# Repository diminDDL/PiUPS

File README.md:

# The DDL pi UPS

# Terms of use
### The following conditions should be met if you want to use any part of this repository:

By using this project or its parts, for any purpose and in any shape or form, you grant your **implicit agreement** to all the following statements:

- You **condemn Russia and its military aggression against Ukraine**
- You **recognize that Russia is an occupant that unlawfully invaded a sovereign state**
- You **support Ukraine's territorial integrity, including its claims over temporarily occupied territories of Crimea and Donbas**
- You **reject false narratives perpetuated by Russian state propaganda**

To learn more about the war and how you can help, [click here](https://u24.gov.ua/). Glory to Ukraine! 🇺🇦

### AND

## CERN Open Hardware Licence v2 (CERN-OHL-W) TL;DR

- **Can:**
  - *Use*: You are free to use the hardware design in any way.
  - *Modify*: You can make modifications to the design.
  - *Distribute*: You can share the original or modified design with others.
  - *Commercial Use*: You can use the design in commercial projects.

- **Can't:**
  - *Hold Liable*: The original author is not liable for any damages or consequences resulting from the use of the design.

- **Conditions:**
  - *Attribution*: You must give appropriate credit to the original author, including a copyright notice, a link to the license, and an indication of any changes made.
  - *ShareAlike*: If you modify the design, you must distribute your contributions under the same license as the original.
  - *License Notice*: You must include a copy of the CERN-OHL-W v2 with the distributed design or provide a clear link to the license.

Disclaimer: This summary is not a legal document and does not provide legal advice. Please read the full license text for a complete understanding of its terms and conditions.

## Info

This repo contains the hardware and *soon TM* software for the ultra efficient raspberry pi UPS.
The reason this was created was because I wasn't satisfied with the things available on the market
that would just lower the incoming voltage to charge the battery and immediately boost it to power the pi. This way efficiencies of around ~80% can be achieved. Don't get me wrong this is not terrible but I wanted to do better, which is why this design incorporates a power MUX.

### Current revision: 0.5

##### Known issues of rev 0.5

| Issue  | Possible fix |
| ------------- |:-------------:|
| Power mux and everything involving the comparator oscilates when trying to shut down. | Use TL431 instead, it combines a voltage reference and a comparator. |
| Turning switch off while plugged in doesn't turn off the output. | Rework the schematic. |
| DW01 chip is acting up (high leakage, not working half of the time). | Replace with BQ2970. |
| BMS turns off when the charger is plugged in. | Try removing diodes going to the fs8205. |

### Pictures

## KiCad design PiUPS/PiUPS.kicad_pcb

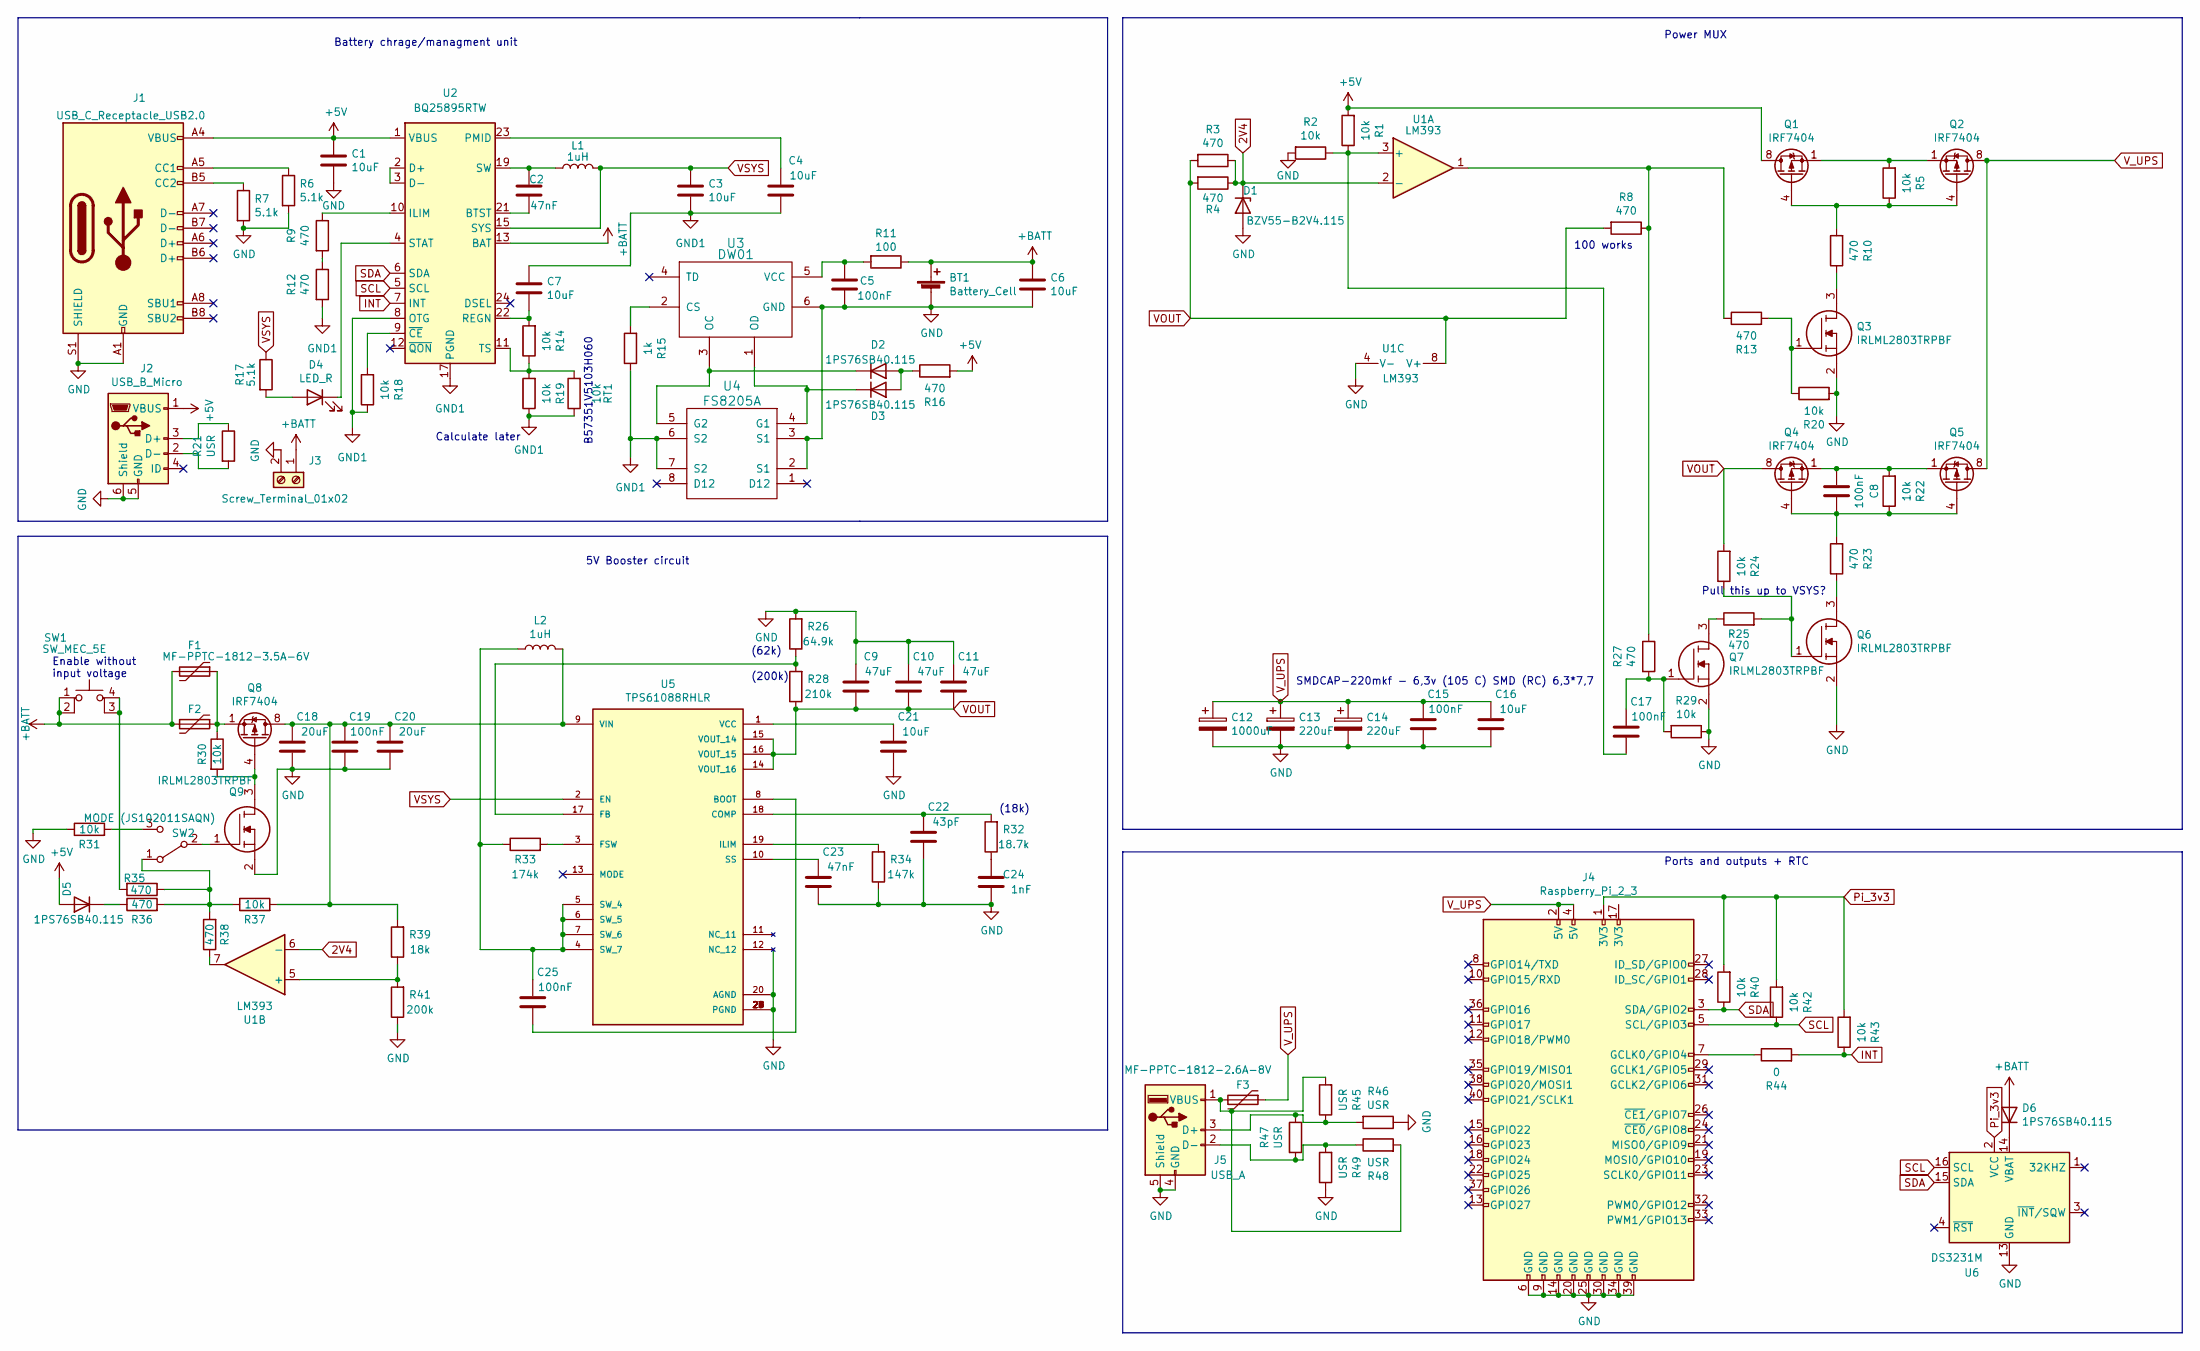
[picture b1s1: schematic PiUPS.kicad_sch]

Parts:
BT1: Battery_Cell; BatteryHolder_Keystone_1042_1x18650
C1, C3, C4, C6, C7, C16, C21: 10uF; C_1206_3216Metric_Pad1.33x1.80mm_HandSolder
C2, C23: 47nF; C_0805_2012Metric_Pad1.18x1.45mm_HandSolder
C5, C8, C15, C17, C19, C25: 100nF; C_0805_2012Metric_Pad1.18x1.45mm_HandSolder
C9, C10, C11: 47uF; C_1210_3225Metric_Pad1.33x2.70mm_HandSolder
C12: 1000uF; CP_Elec_10x10
C13, C14: 220uF; CP_Elec_6.3x7.7
C18, C20: 20uF; C_1206_3216Metric_Pad1.33x1.80mm_HandSolder
C22: 43pF; C_0805_2012Metric_Pad1.18x1.45mm_HandSolder
C24: 1nF; C_0805_2012Metric_Pad1.18x1.45mm_HandSolder
D1: BZV55-B2V4.115; D_1206_3216Metric_Pad1.42x1.75mm_HandSolder
D2, D3, D5, D6: 1PS76SB40.115; D_SOD-323_HandSoldering
D4: LED_R; LED_1206_3216Metric_Pad1.42x1.75mm_HandSolder
F1, F2: MF-PPTC-1812-3.5A-6V; Fuse_1812_4532Metric_Pad1.30x3.40mm_HandSolder
F3: MF-PPTC-1812-2.6A-8V; Fuse_1812_4532Metric_Pad1.30x3.40mm_HandSolder
J1: USB_C_Receptacle_USB2.0; USB_C_Receptacle_Palconn_UTC16-G
J2: USB_B_Micro; USB_Micro-B_Amphenol_10103594-0001LF_Horizontal
J3: Screw_Terminal_01x02; TerminalBlock_Altech_AK300-2_P5.00mm
J4: Raspberry_Pi_2_3; raspberrypi_2_3
J5: USB_A; SAMTEC_USB-A-S-X-X-SM2
L1: 1uH; L_6.3x6.3_H3
L2: 1uH; L_10.4x10.4_H4.8
Q1, Q2, Q4, Q5, Q8: IRF7404; SOIC-8_3.9x4.9mm_P1.27mm
Q3, Q6, Q7, Q9: IRLML2803TRPBF; SOT95P237X112-3N; Manufacturer_Part_Number IRLML2803TRPBF; Mouser Part Number 942-IRLML2803TRPBF
R1, R2, R5, R14, R18, R19, R20, R22, R24, R29, R30, R31, R37, R40, R42, R43: 10k; R_0805_2012Metric_Pad1.20x1.40mm_HandSolder
R3, R4, R8, R9, R10, R12, R13, R16, R23, R25, R27, R35, R36, R38: 470; R_0805_2012Metric_Pad1.20x1.40mm_HandSolder
R6, R7, R17: 5.1k; R_0805_2012Metric_Pad1.20x1.40mm_HandSolder
R11: 100; R_0805_2012Metric_Pad1.20x1.40mm_HandSolder
R15: 1k; R_0805_2012Metric_Pad1.20x1.40mm_HandSolder
R21, R45, R46, R47, R48, R49: USR; R_0805_2012Metric_Pad1.20x1.40mm_HandSolder
R26: 64.9k; R_0805_2012Metric_Pad1.20x1.40mm_HandSolder
R28: 210k; R_0805_2012Metric_Pad1.20x1.40mm_HandSolder
R32: 18.7k; R_0805_2012Metric_Pad1.20x1.40mm_HandSolder
R33: 174k; R_0805_2012Metric_Pad1.20x1.40mm_HandSolder
R34: 147k; R_0805_2012Metric_Pad1.20x1.40mm_HandSolder
R39: 18k; R_0805_2012Metric_Pad1.20x1.40mm_HandSolder
R41: 200k; R_0805_2012Metric_Pad1.20x1.40mm_HandSolder
R44: 0; R_0805_2012Metric_Pad1.20x1.40mm_HandSolder
RT1: 10k; R_0603_1608Metric
SW1: SW_MEC_5E; SW_SPST_Omron_B3FS-100xP
SW2: MODE (JS102011SAQN); SW_SPDT_CK-JS102011SAQN
U1: LM393; SOIC-8_3.9x4.9mm_P1.27mm
U2: BQ25895RTW; Texas_S-PWQFN-N24_EP2.7x2.7mm_ThermalVias
U3: DW01; SOT-23-6
U4: FS8205A; TSSOP-8_4.4x3mm_P0.65mm
U5: TPS61088RHLR; IC_TPS61088RHLR; PARTREV 4219071/A 05/2017
U6: DS3231M; SOIC-16W_7.5x10.3mm_P1.27mm

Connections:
2V4: D1.1 (K), R3.1, R4.1, U1.2 (-), U1.6 (-)
+5V: C1.1, D5.2 (A), J1.A4 (VBUS), J1.A9 (VBUS), J1.B4 (VBUS), J1.B9 (VBUS), J2.1 (VBUS), Q1.5 (D), Q1.6 (D), Q1.7 (D), Q1.8 (D), R1.2, R16.2, U2.1 (VBUS)
+BATT: BT1.1 (+), C6.1, D6.2 (A), F1.2, F2.2, J3.1, R11.1, SW1.1, SW1.2, U2.13 (BAT), U2.14 (BAT)
GND: BT1.2 (-), C1.2, C5.2, C6.2, C9.1, C10.1, C11.1, C12.2, C13.2, C14.2, C15.2, C16.2, C18.2, C19.2, C20.2, C21.2, C22.2, C23.2, C24.2, D1.2 (A), J1.A1 (GND), J1.A12 (GND), J1.B1 (GND), J1.B12 (GND), J1.S1 (SHIELD), J2.5 (GND), J2.6 (Shield), J3.2, J4.6 (GND), J4.9 (GND), J4.14 (GND), J4.20 (GND), J4.25 (GND), J4.30 (GND), J4.34 (GND), J4.39 (GND), J5.4 (GND), J5.5 (Shield), Q3.2, Q6.2, Q7.2, Q9.2, R2.2, R6.2, R7.2, R20.2, R26.2, R29.1, R31.1, R34.1, R41.1, R46.1, R49.1, U1.4 (V-), U3.6 (GND), U4.2 (S1), U4.3 (S1), U5.12 (NC_12), U5.20 (AGND), U5.21 (PGND), U5.22 (PGND), U5.23 (PGND), U5.24 (PGND), U5.25 (PGND), U5.26 (PGND), U5.27 (PGND), U5.28 (PGND), U5.29 (PGND), U6.5 (GND), U6.6 (GND), U6.7 (GND), U6.8 (GND), U6.9 (GND), U6.10 (GND), U6.11 (GND), U6.12 (GND), U6.13 (GND); also elsewhere on the board
GND1: C3.2, C4.2, C7.1, R12.2, R15.1, R18.1, R19.1, RT1.1, U2.8 (OTG), U2.17 (PGND), U2.18 (PGND), U2.25 (PGND), U4.6 (S2), U4.7 (S2)
INT: R43.1, R44.2, U2.7 (INT)
unnamed: C2.1, L1.1, U2.19 (SW), U2.20 (SW)
unnamed: C2.2, U2.21 (BTST)
unnamed: C4.1, U2.23 (PMID)
unnamed: C5.1, R11.2, U3.5 (VCC)
unnamed: C7.2, R14.2, U2.22 (REGN)
unnamed: C8.1, Q4.1 (S), Q4.2 (S), Q4.3 (S), Q5.1 (S), Q5.2 (S), Q5.3 (S), R22.2
unnamed: C8.2, Q4.4 (G), Q5.4 (G), R22.1, R23.2
unnamed: C17.1, Q7.1, R27.2, R29.2
unnamed: C17.2, R1.1, R2.1, U1.3 (+)
unnamed: C18.1, C19.1, C20.1, L2.2, Q8.5 (D), Q8.6 (D), Q8.7 (D), Q8.8 (D), R37.2, R39.2, U5.9 (VIN)
unnamed: C21.1, U5.1 (VCC)
unnamed: C22.1, R32.2, U5.18 (COMP)
unnamed: C23.1, U5.10 (SS)
unnamed: C24.1, R32.1
unnamed: C25.1, L2.1, R33.1, U5.4 (SW_7), U5.5 (SW_4), U5.6 (SW_5), U5.7 (SW_6)
unnamed: C25.2, U5.8 (BOOT)
unnamed: D2.1 (K), U3.3 (OC), U4.5 (G2)
unnamed: D2.2 (A), D3.2 (A), R16.1
unnamed: D3.1 (K), U3.1 (OD), U4.4 (G1)
unnamed: D4.1 (K), U2.4 (STAT)
unnamed: D4.2 (A), R17.2
unnamed: D5.1 (K), R36.1
unnamed: D6.1 (K), U6.14 (VBAT)
unnamed: F1.1, F2.1, Q8.1 (S), Q8.2 (S), Q8.3 (S), R30.1
unnamed 30: F3.2, J5.1 (VBUS), R45.2, R48.2; also elsewhere on the board
unnamed: J1.A5 (CC1), R6.1
unnamed: J1.B5 (CC2), R7.1
unnamed: J2.2 (D-), R21.2
unnamed: J2.3 (D+), R21.1
unnamed: J4.7 (GCLK0/GPIO4), R44.1
unnamed: J5.2 (D-), R47.2, R48.1, R49.2
unnamed: J5.3 (D+), R45.1, R46.2, R47.1
unnamed: Q1.1 (S), Q1.2 (S), Q1.3 (S), Q2.1 (S), Q2.2 (S), Q2.3 (S), R5.2
unnamed: Q1.4 (G), Q2.4 (G), R5.1, R10.2
unnamed: Q3.1, R13.2, R20.1
unnamed: Q3.3, R10.1
unnamed: Q6.1, R24.1, R25.2
unnamed: Q6.3, R23.1
unnamed: Q7.3, R25.1
unnamed: Q8.4 (G), Q9.3, R30.2
unnamed: Q9.1, SW2.2 (B)
unnamed: R9.1, U2.10 (ILIM)
unnamed: R9.2, R12.1
unnamed: R8.1, R13.1, R27.1, U1.1
unnamed: R14.1, R19.2, RT1.2, U2.11 (TS)
unnamed: R15.2, U3.2 (CS)
unnamed: R18.2, U2.9 (~CE)
unnamed: R26.1, R28.2, U5.17 (FB)
unnamed: R31.2, SW2.3 (C)
unnamed: R33.2, U5.3 (FSW)
unnamed: R34.2, U5.19 (ILIM)
unnamed: R35.1, R36.2, R37.1, R38.2, SW2.1 (A)
unnamed: R35.2, SW1.3 (K), SW1.4 (A)
unnamed: R38.1, U1.7
unnamed: R39.1, R41.2, U1.5 (+)
unnamed: U2.2 (D+), U2.3 (D-)
Pi_3v3: J4.1 (3V3), R40.2, R42.2, R43.2, U6.2 (VCC)
SCL: J4.5 (SCL/GPIO3), R42.1, U2.5 (SCL), U6.16 (SCL)
SDA: J4.3 (SDA/GPIO2), R40.1, U2.6 (SDA), U6.15 (SDA)
VOUT: C9.2, C10.2, C11.2, Q4.5 (D), Q4.6 (D), Q4.7 (D), Q4.8 (D), R3.2, R4.2, R8.2, R24.2, R28.1, U1.8 (V+), U5.14 (VOUT_16), U5.15 (VOUT_14), U5.16 (VOUT_15)
VSYS: C3.1, L1.2, R17.1, U2.15 (SYS), U2.16 (SYS), U5.2 (EN)
V_UPS: C12.1, C13.1, C14.1, C15.1, C16.1, F3.1, J4.2 (5V), J4.4 (5V), Q2.5 (D), Q2.6 (D), Q2.7 (D), Q2.8 (D), Q5.5 (D), Q5.6 (D), Q5.7 (D), Q5.8 (D)

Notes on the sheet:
Enable without input voltage
Battery chrage/managment unit
Ports and outputs + RTC
5V Booster circuit
Calculate later
(200k)
(18k)
Power MUX
Pull this up to VSYS?
(62k)
B57351V5103H060
SMDCAP-220mkf - 6,3v (105 С) SMD (RC) 6,3*7,7
100 works

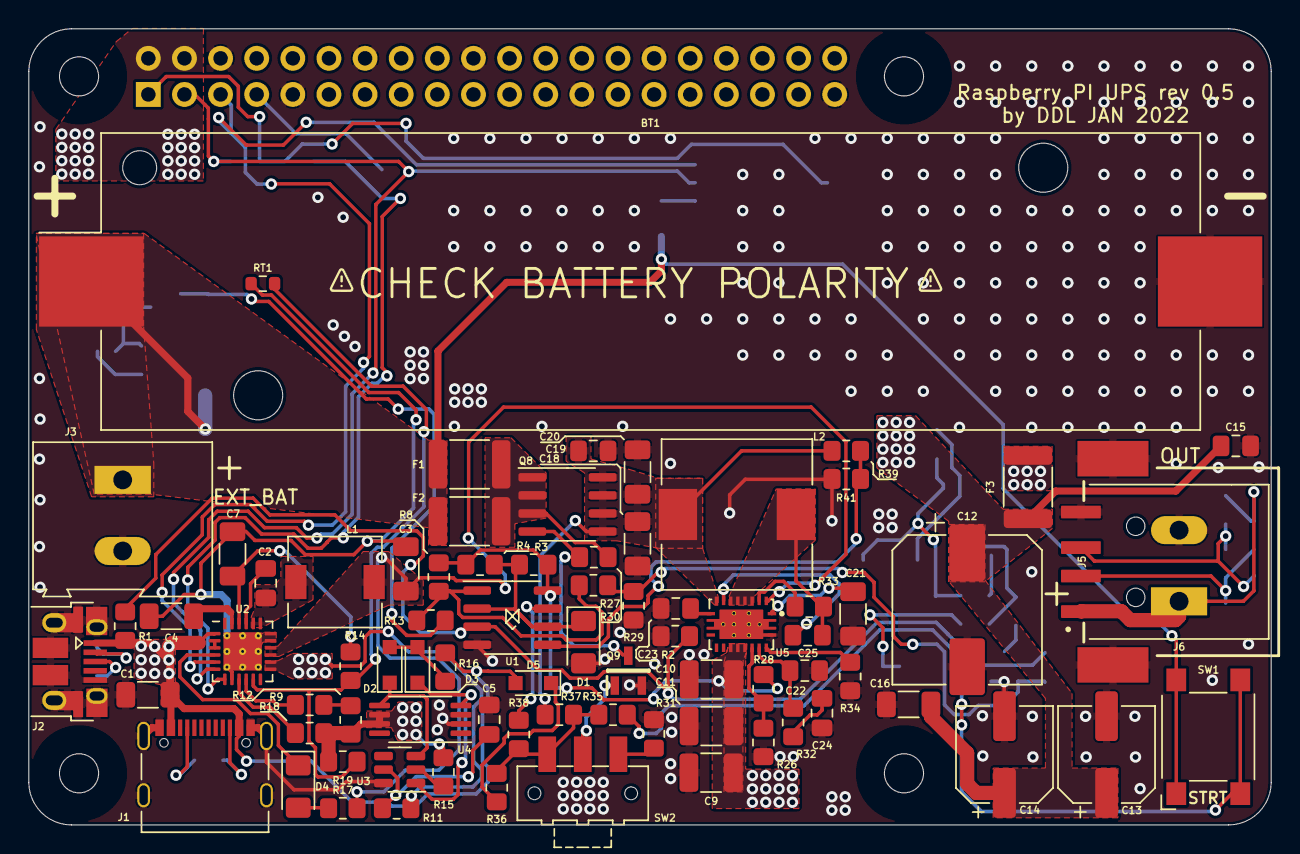
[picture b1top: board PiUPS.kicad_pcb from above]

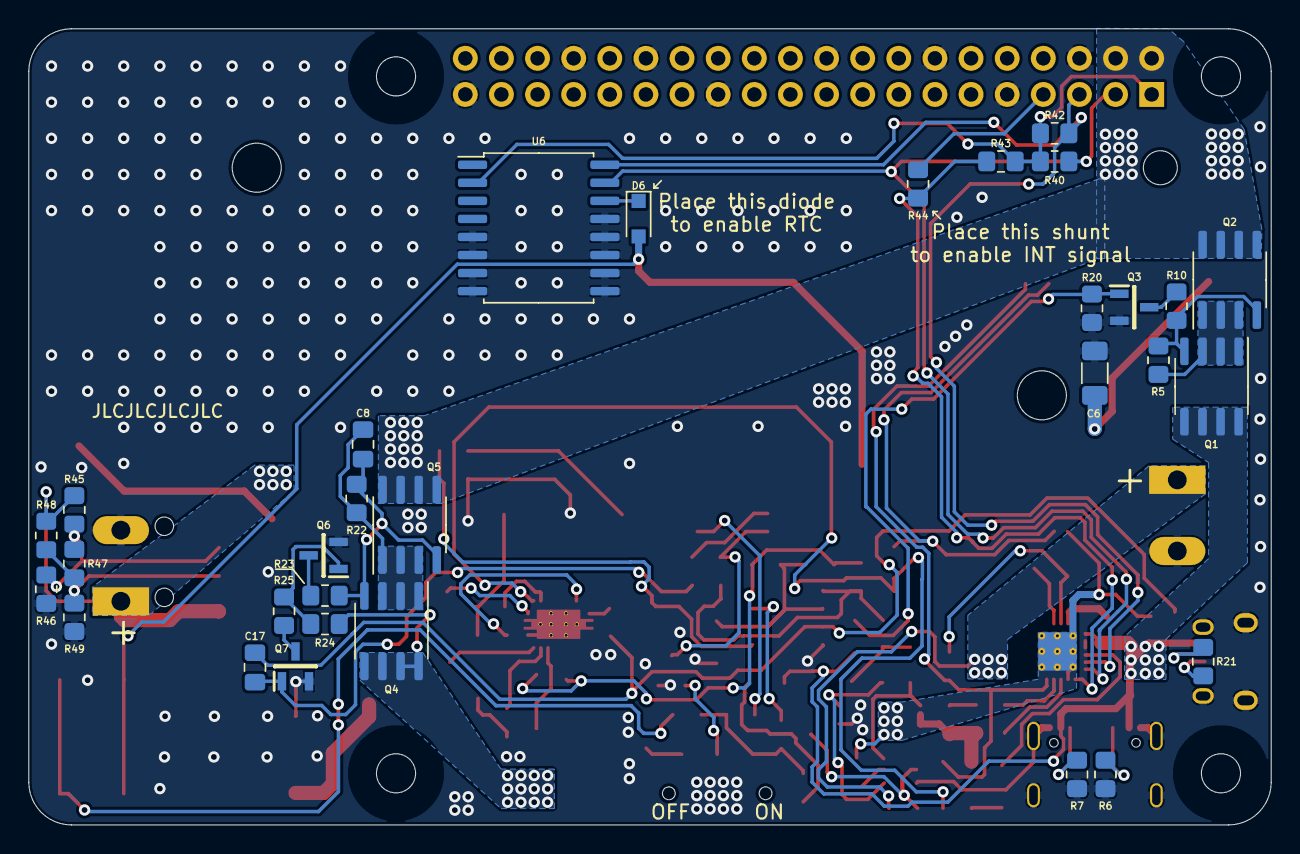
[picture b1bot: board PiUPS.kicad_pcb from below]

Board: 2 copper layers, 87.4 x 56.0 mm, 110 parts (31 on the bottom side), 68 nets.

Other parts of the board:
J6: Screw_Terminal_01x02; TerminalBlock_Altech_AK300-2_P5.00mm

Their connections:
GND: J6.2; also elsewhere on the board
unnamed 30: J6.1; also elsewhere on the board

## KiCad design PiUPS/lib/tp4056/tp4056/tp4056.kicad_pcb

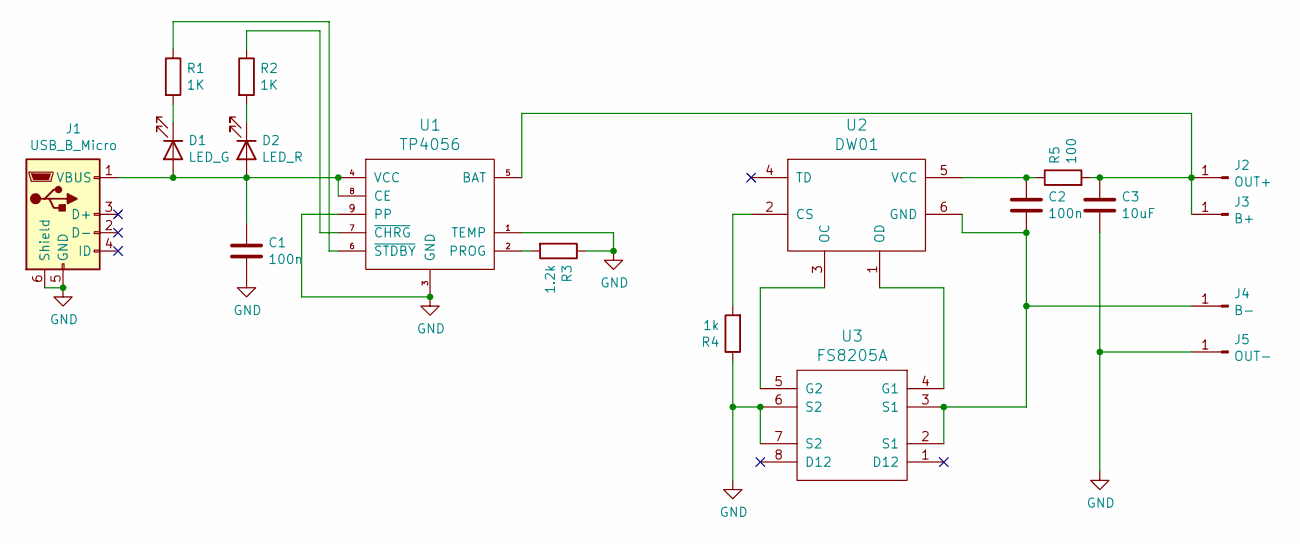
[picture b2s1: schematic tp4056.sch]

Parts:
C1, C2: 100n; C_0402_1005Metric_Pad0.74x0.62mm_HandSolder
C3: 10uF; C_0805_2012Metric_Pad1.18x1.45mm_HandSolder
D1: LED_G; C_0805_2012Metric_Pad1.18x1.45mm_HandSolder
D2: LED_R; C_0805_2012Metric_Pad1.18x1.45mm_HandSolder
J1: USB_B_Micro; USB_Micro-AB_Molex_47590-0001
J2: OUT+; PinHeader_1x01_P2.54mm_Vertical
J3: B+; PinHeader_1x01_P2.54mm_Vertical
J4: B-; PinHeader_1x01_P2.54mm_Vertical
J5: OUT-; PinHeader_1x01_P2.54mm_Vertical
R1, R2: 1K; R_0805_2012Metric_Pad1.20x1.40mm_HandSolder
R3: 1.2k; R_0805_2012Metric_Pad1.20x1.40mm_HandSolder
R4: 1k; R_0805_2012Metric_Pad1.20x1.40mm_HandSolder
R5: 100; R_0805_2012Metric_Pad1.20x1.40mm_HandSolder
U1: TP4056; SOIC-8-1EP_3.9x4.9mm_P1.27mm_EP2.29x3mm
U2: DW01; TSOP-6_1.65x3.05mm_P0.95mm
U3: FS8205A; TSSOP-8_4.4x3mm_P0.65mm

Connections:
GND: C1.2, C3.2, J1.5 (GND), J1.6 (Shield), J5.1, R3.1, R4.1, U1.1 (TEMP), U1.3 (GND), U1.9 (PP), U3.6 (S2), U3.7 (S2)
unnamed: C1.1, D1.2 (A), D2.2 (A), J1.1 (VBUS), U1.4 (VCC), U1.8 (CE)
unnamed: C2.1, R5.1, U2.5 (VCC)
unnamed: C2.2, J4.1, U2.6 (GND), U3.2 (S1), U3.3 (S1)
unnamed: C3.1, J2.1, J3.1, R5.2, U1.5 (BAT)
unnamed: D1.1 (K), R1.2
unnamed: D2.1 (K), R2.2
unnamed: R1.1, U1.6 (~STDBY)
unnamed: R2.1, U1.7 (~CHRG)
unnamed: R3.2, U1.2 (PROG)
unnamed: R4.2, U2.2 (CS)
unnamed: U2.1 (OD), U3.4 (G1)
unnamed: U2.3 (OC), U3.5 (G2)

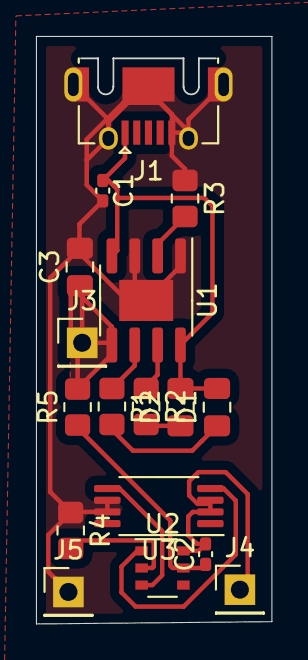
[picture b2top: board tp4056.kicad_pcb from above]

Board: 2 copper layers, 13.0 x 32.6 mm, 17 parts (0 on the bottom side), 13 nets.

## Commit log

2021-08-07 initial commit
    First upload
2021-09-18 Updated to include the boges to rev 0.2
2021-09-18 Create LICENSE
2021-10-11 added exprimental latching boost IC cutoff circuit + notes about dev branch file and future things to do
2021-10-23 updated debug schematic
2021-12-12 added almost final fixes for rev 0.1
2021-12-20 tidied up schematic
2021-12-26 updated to Kicad 6.0
2021-12-26 minor improvements and cleanup
2021-12-26 added label on PCB to indicate that it is outdated
2021-12-26 minor changes
2022-01-16 assigned footprints
2022-01-18 beginning of routing
2022-01-18 Continued routing
2022-01-21 almost finished routing
2022-01-22 finshed layout and routing
2022-01-23 silkscreen orginization
2022-01-24 finished routing new PCB
2022-01-26 finalized PCB layout
2022-02-02 rev 0.5 update (#2)
    * added exprimental latching boost IC cutoff circuit + notes about dev branch file and future things to do
    * updated debug schematic
    * added almost final fixes for rev 0.1
    * tidied up schematic
    * updated to Kicad 6.0
    * minor improvements and cleanup
2022-02-02 Fixed DRC issues
2022-02-02 added new gerbers
2022-04-27 minor touchups
2022-05-10 minour improvements
2022-07-07 updated development schematic
2022-07-07 added updated pdf
2022-07-18 updated components and schematic sligtly
2022-07-19 updated pdf
2022-09-15 updated shcematic with new battery protection system and some notes
2022-09-18 changed some values
2022-09-22 working on fixing some design mistakes
2022-11-06 added possible comparator replacement schematics
2022-12-21 uploaded assets
2023-04-29 minor schematic changes
2023-04-29 update licence
